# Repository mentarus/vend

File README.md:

Kicad files for motor driver board

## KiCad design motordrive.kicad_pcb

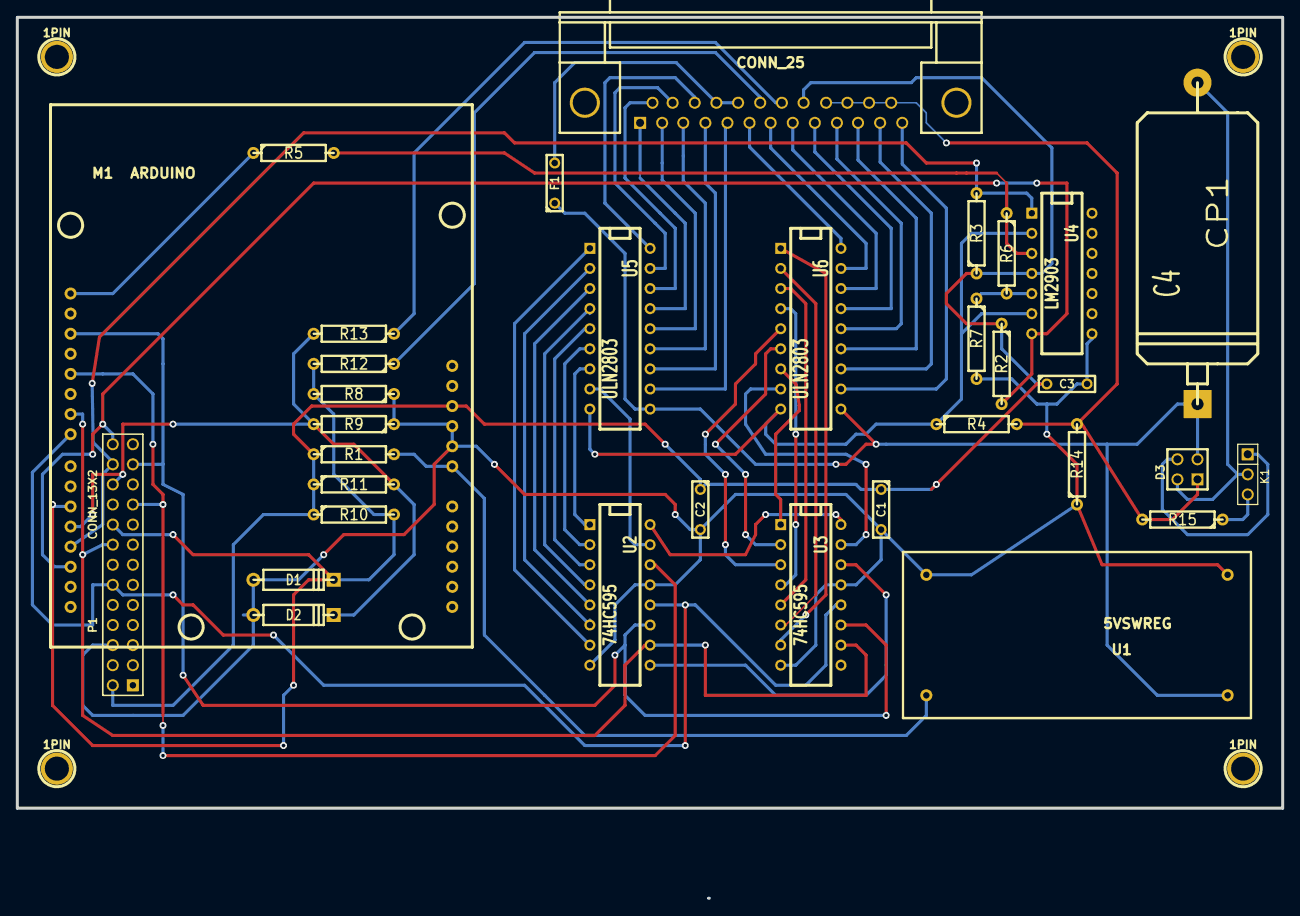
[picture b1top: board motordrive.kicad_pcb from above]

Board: 2 copper layers, 160.0 x 111.4 mm, 37 parts (0 on the bottom side), 57 nets.

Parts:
1PIN, 1PIN#2, 1PIN#3, 1PIN#4: P***; 1pin
C1, C2, C3: C; C2
C4: CP1; CP16
D1, D2: 3v3; D4
D3: BRIDGE; PIN_ARRAY_2X2
F1: FUSE; C2
K1: CONN_3; PIN_ARRAY_3X1
M1: ARDUINO; Arduino_rev
P1: CONN_13X2; pin_array_13x2
P2: CONN_25; DB25FC
R1: n/f; R4
R2, R3: 4k7; R4
R4: 1R5; R4
R5, R6, R7: R; R4
R8, R9, R10, R11: 8k2; R4
R12, R13: 2k2; R4
R14, R15: 0R; R4
U1: 5VSWREG; SWREG-X4
U2, U3: 74HC595; DIP-16__300
U4: LM2903; DIP-14__300
U5, U6: ULN2803; DIP-18__300

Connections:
+5V: C1.1, C2.1, C3.1, M1.3, P1.2, P2.21, R1.1, R2.1, R3.1, R10.1, R11.1, U4.4
+24V: C4.1, D3.3, F1.1, U1.4, U5.10, U6.10
/30mV: R6.2, R7.1, U4.5
/640mV: R5.2, R6.1, U4.3
GND: C1.2, C2.2, C3.2, D1.1, D2.1, M1.4, M1.5, P1.6, R7.2, R8.1, R9.1, R14.1, U1.1, U1.2, U2.8, U2.13, U3.8, U3.13, U4.8
GNDA: D3.1, P2.22, P2.23, P2.24, P2.25, R4.2, R14.2, R15.2
unnamed: F1.2, P2.17, P2.18
unnamed: D3.4, K1.1
unnamed: U2.9, U3.14
unnamed: P2.20, R13.1
unnamed: M1.28, R5.1
unnamed: R4.1, U4.2, U4.6, U5.9, U6.9
unnamed: P2.9, U6.15
unnamed: P2.1, U5.15
unnamed: P2.15, U5.17
unnamed: P2.13, U6.11
unnamed: P2.12, U6.12
unnamed: P2.10, U6.14
unnamed: P2.3, U5.13
unnamed: P2.7, U6.17
unnamed: U2.2, U5.6
unnamed: U3.15, U6.8
unnamed: U2.6, U5.2
unnamed: U2.4, U5.4
unnamed: U2.1, U5.7
unnamed: M1.22, P1.16, U2.10, U3.10
unnamed: P2.16, U5.18
unnamed: P2.14, U5.16
unnamed: P2.2, U5.14
unnamed: P2.5, U5.11
unnamed: M1.16, P1.24, R3.2, U4.1
unnamed: P2.8, U6.16
unnamed: P2.6, U6.18
unnamed: P2.11, U6.13
unnamed: M1.15, P1.26, R2.2, U4.7
unnamed: M1.26, P1.23, U2.11, U3.11
unnamed: P2.4, U5.12
unnamed: U2.7, U5.1
unnamed: U3.1, U6.7
unnamed: U3.3, U6.5
unnamed: U3.5, U6.3
unnamed: D1.2, M1.18, P1.18, R8.2, R10.2, R12.2
unnamed: P2.19, R12.1
unnamed: U2.15, U5.8
unnamed: U2.3, U5.5
unnamed: U2.5, U5.3
unnamed: D2.2, M1.17, P1.22, R9.2, R11.2, R13.2
unnamed: K1.3, R15.1
unnamed: M1.21, P1.12, U2.12, U3.12
unnamed: M1.24, P1.19, U2.14
unnamed: M1.6, R1.2, U1.3
unnamed: C4.2, D3.2, K1.2
unnamed: U3.7, U6.1
unnamed: U3.6, U6.2
unnamed: U3.4, U6.4
unnamed: U3.2, U6.6
VCC: U2.16, U3.16

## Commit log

2014-01-17 repo created
2014-01-17 initial checkin
2014-02-21 Added raspberry pi connector Replaced cabinet connector with D25 Added power & input pins for cabinet connector Added power supply Corrected pin assigments to place MOSI and SCK to shift regs
2014-03-10 schematic completed
2014-03-10 Initial board placement
2014-03-10 Added library modules
2014-03-11 Change schematic to ease routing partially routed
2014-04-26 small updates to layout
2014-06-15 Merged in Paddy's routing changes
2014-07-20 Enlarged tracks to 0.4mm
